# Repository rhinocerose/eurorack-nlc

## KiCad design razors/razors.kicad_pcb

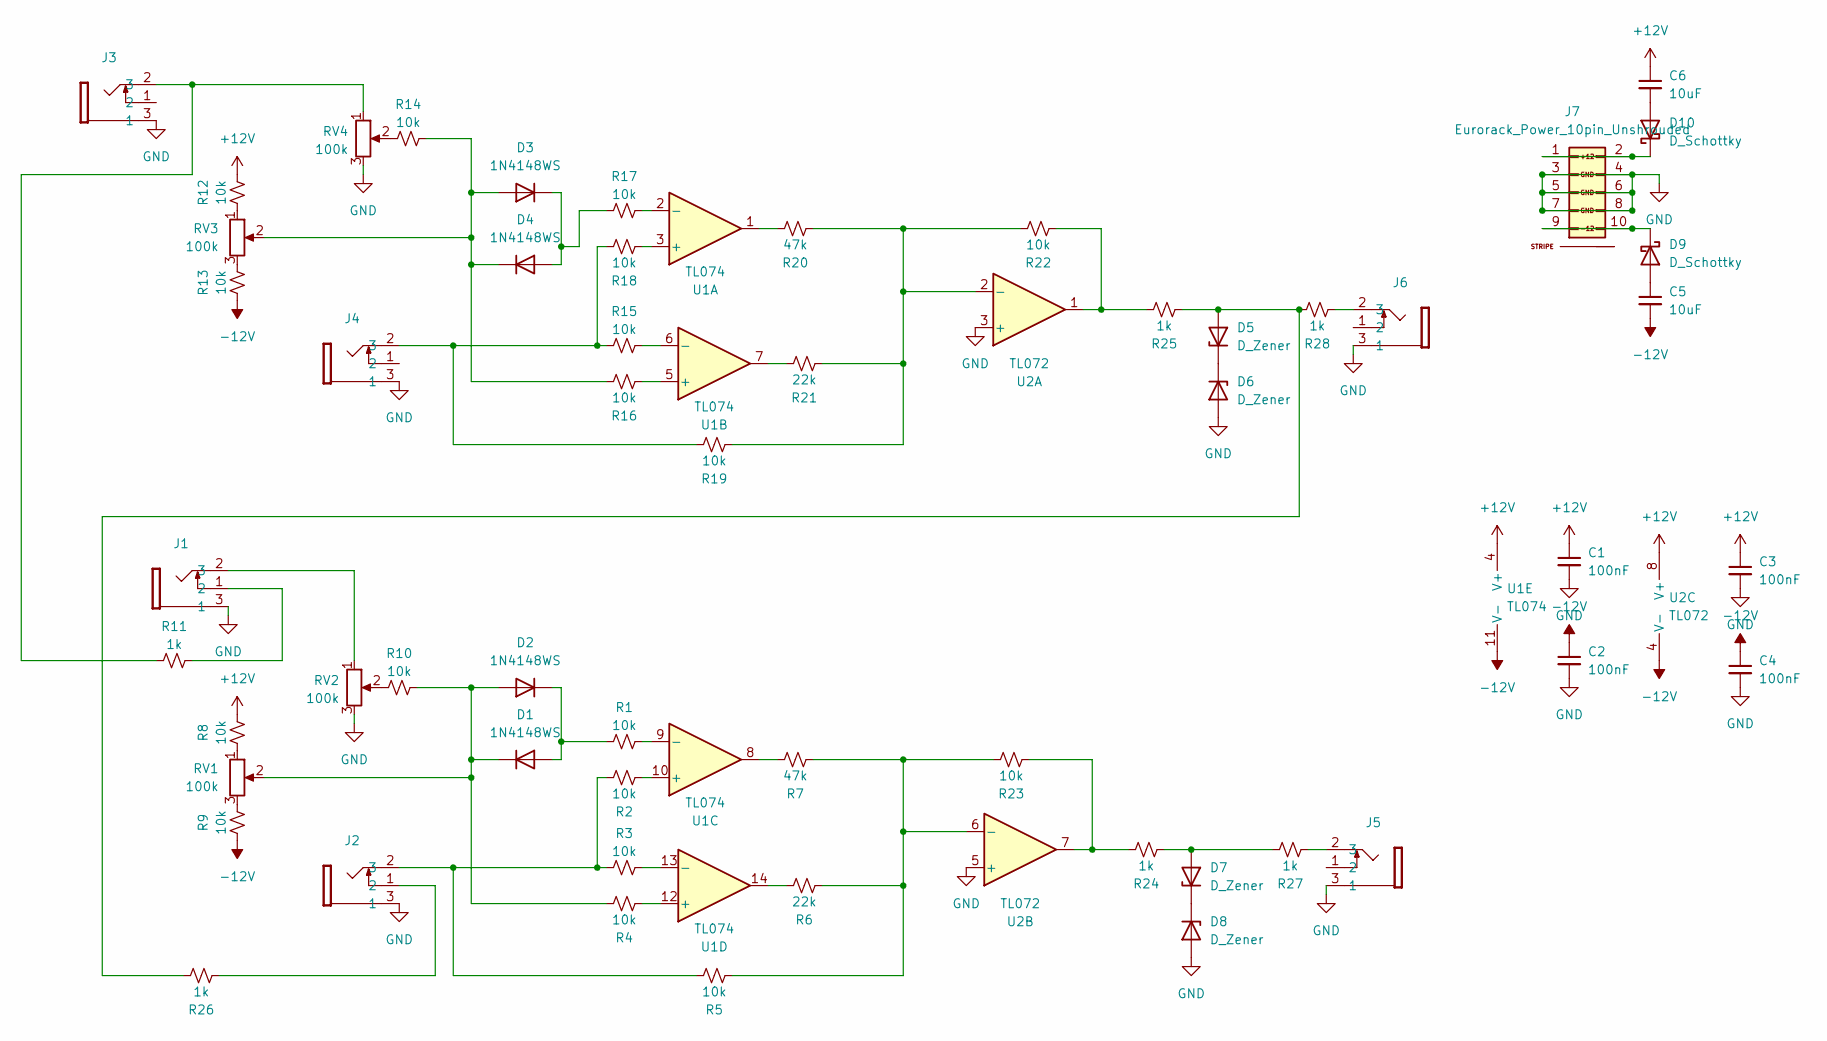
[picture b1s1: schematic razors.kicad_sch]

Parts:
C1, C2, C3, C4: 100nF; C_0603_1608Metric
C5, C6: 10uF; C_0805_2012Metric
D1, D2, D3, D4: 1N4148WS; D_SOD-323
D5, D6, D7, D8: D_Zener; D_SOD-323
D9, D10: D_Schottky; D_SOD-323
J1, J2, J3, J4, J5, J6: Thonkiconn-Jack
J7: Eurorack_Power_10pin_Unshrouded; PinHeader_2x05_P2.54mm_Vertical; Part Number 1-1002FBV0T
R1, R2, R3, R4, R5, R8, R9, R10, R12, R13, R14, R15, R16, R17, R18, R19, R22, R23: 10k; R_0603_1608Metric
R6, R21: 22k; R_0603_1608Metric
R7, R20: 47k; R_0603_1608Metric
R11, R24, R25, R26, R27, R28: 1k; R_0603_1608Metric
RV1, RV2, RV3, RV4: 100k; Potentiometer_Alps_RK09K_Single_Vertical
U1: TL074; TSSOP-14_4.4x5mm_P0.65mm
U2: TL072; TSSOP-8_4.4x3mm_P0.65mm

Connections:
+12V: C1.1, C3.1, C6.1, R8.2, R12.2, U1.4 (V+), U2.8 (V+)
-12V: C2.1, C4.1, C5.2, R9.1, R13.1, U1.11 (V-), U2.4 (V-)
GND: C1.2, C2.2, C3.2, C4.2, D6.2 (A), D8.2 (A), J1.3 (1), J2.3 (1), J3.3 (1), J4.3 (1), J5.3 (1), J6.3 (1), J7.3 (GND), J7.4 (GND), J7.5 (GND), J7.6 (GND), J7.7 (GND), J7.8 (GND), RV2.3, RV4.3, U2.3 (+), U2.5 (+)
unnamed: D1.2 (A), D2.1 (K), R1.1
unnamed: D1.1 (K), D2.2 (A), R4.2, R10.2, RV1.2
unnamed: D3.2 (A), D4.1 (K), R14.2, R16.2, RV3.2
unnamed: D3.1 (K), D4.2 (A), R17.1
unnamed: D5.2 (A), R25.1, R26.2, R28.2
unnamed: D5.1 (K), D6.1 (K)
unnamed: D7.2 (A), R24.1, R27.2
unnamed: D7.1 (K), D8.1 (K)
unnamed: C5.1, D9.2 (A)
unnamed: D9.1 (K), J7.9 (-12V), J7.10 (-12V)
unnamed: C6.2, D10.2 (A)
unnamed: D10.1 (K), J7.1 (+12V), J7.2 (+12V)
unnamed: J1.1 (2), R11.2
unnamed: J1.2 (3), RV2.1
unnamed: J2.1 (2), R26.1
unnamed: J2.2 (3), R2.2, R3.1, R5.2
unnamed: J3.2 (3), R11.1, RV4.1
unnamed: J4.2 (3), R15.1, R18.2, R19.2
unnamed: J5.2 (3), R27.1
unnamed: J6.2 (3), R28.1
unnamed: R6.2, U1.14
unnamed: R7.2, U1.8
unnamed: R8.1, RV1.1
unnamed: R9.2, RV1.3
unnamed: R10.1, RV2.2
unnamed: R12.1, RV3.1
unnamed: R13.2, RV3.3
unnamed: R14.1, RV4.2
unnamed: R20.2, U1.1
unnamed: R21.2, U1.7
unnamed: R22.1, R25.2, U2.1
unnamed: R23.1, R24.2, U2.7
unnamed: R18.1, U1.3 (+)
unnamed: R17.2, U1.2 (-)
unnamed: R16.1, U1.5 (+)
unnamed: R15.2, U1.6 (-)
unnamed: R2.1, U1.10 (+)
unnamed: R1.2, U1.9 (-)
unnamed: R4.1, U1.12 (+)
unnamed: R3.2, U1.13 (-)
unnamed: R19.1, R20.1, R21.1, R22.2, U2.2 (-)
unnamed: R5.1, R6.1, R7.1, R23.2, U2.6 (-)

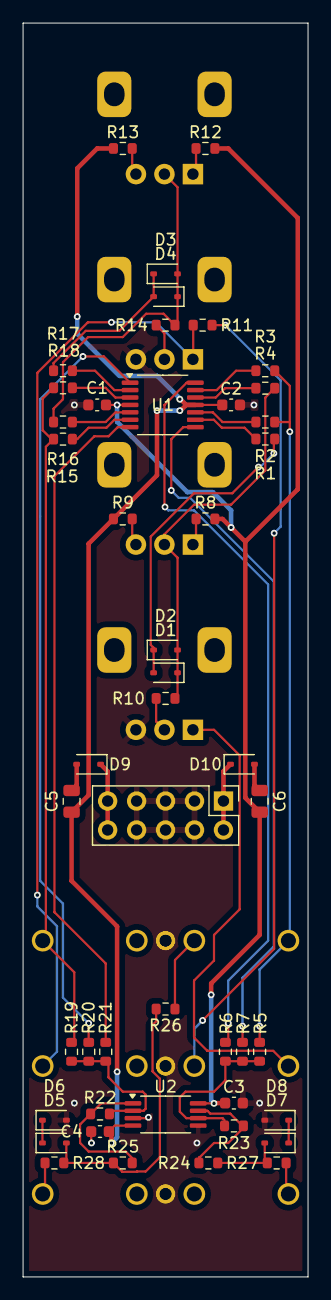
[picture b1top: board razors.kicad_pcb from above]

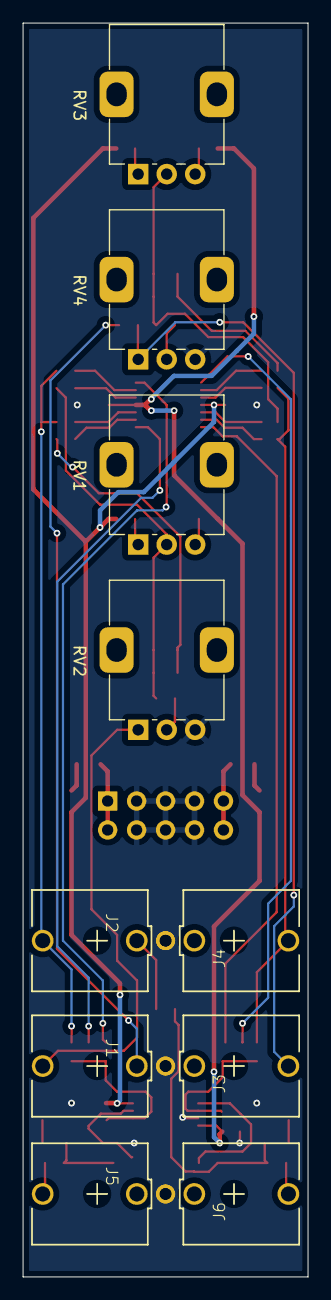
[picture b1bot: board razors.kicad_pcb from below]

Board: 2 copper layers, 25.0 x 110.0 mm, 57 parts (10 on the bottom side), 45 nets.

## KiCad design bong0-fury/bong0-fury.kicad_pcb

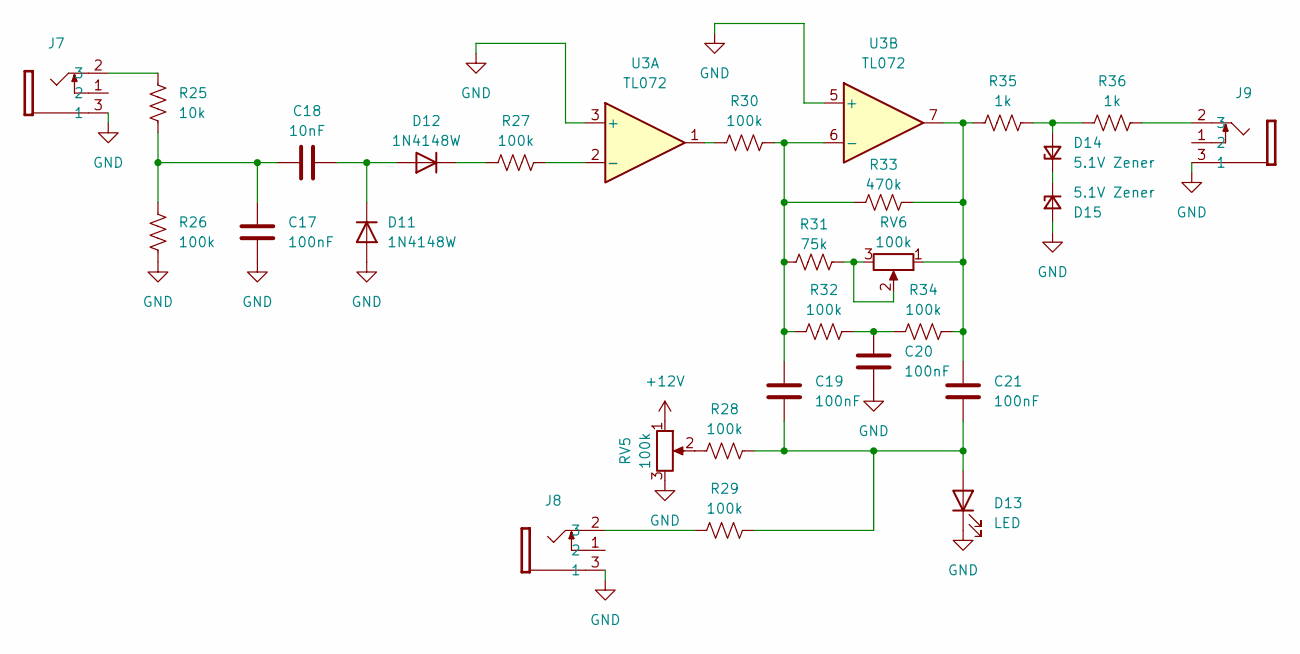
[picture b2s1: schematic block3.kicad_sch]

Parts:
C17, C19, C20, C21: 100nF; C_0603_1608Metric
C18: 10nF; C_0603_1608Metric
D11, D12: 1N4148W; D_SOD-123
D13: LED; LED_D3.0mm
D14, D15: 5.1V Zener; D_SOD-123
J7, J8, J9: Thonkiconn-Jack
R25: 10k; R_0603_1608Metric
R26, R27, R28, R29, R30, R32, R34: 100k; R_0603_1608Metric
R31: 75k; R_0603_1608Metric
R33: 470k; R_0603_1608Metric
R35, R36: 1k; R_0603_1608Metric
RV5, RV6: 100k; Potentiometer_Alps_RK09K_Single_Vertical
U3: TL072; TSSOP-8_4.4x3mm_P0.65mm

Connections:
+12V: RV5.1; also elsewhere on the board
GND: C17.2, C20.2, D11.2 (A), D13.1 (K), D15.2 (A), J7.3 (1), J8.3 (1), J9.3 (1), R26.1, RV5.3, U3.3 (+), U3.5 (+); also elsewhere on the board
unnamed: C17.1, C18.1, R25.2, R26.2
unnamed: C20.1, R32.2, R34.1
unnamed: C21.1, R33.2, R34.2, R35.1, RV6.1, U3.7
unnamed: C18.2, D11.1 (K), D12.2 (A)
unnamed: D12.1 (K), R27.1
unnamed: C19.2, C21.2, D13.2 (A), R28.2, R29.2
unnamed: D14.2 (A), R35.2, R36.1
unnamed: D14.1 (K), D15.1 (K)
unnamed: J7.2 (3), R25.1
unnamed: J8.2 (3), R29.1
unnamed: J9.2 (3), R36.2
unnamed: R28.1, RV5.2
unnamed: R30.1, U3.1
unnamed: R31.2, RV6.2, RV6.3
unnamed: R27.2, U3.2 (-)
unnamed: C19.1, R30.2, R31.1, R32.1, R33.1, U3.6 (-)

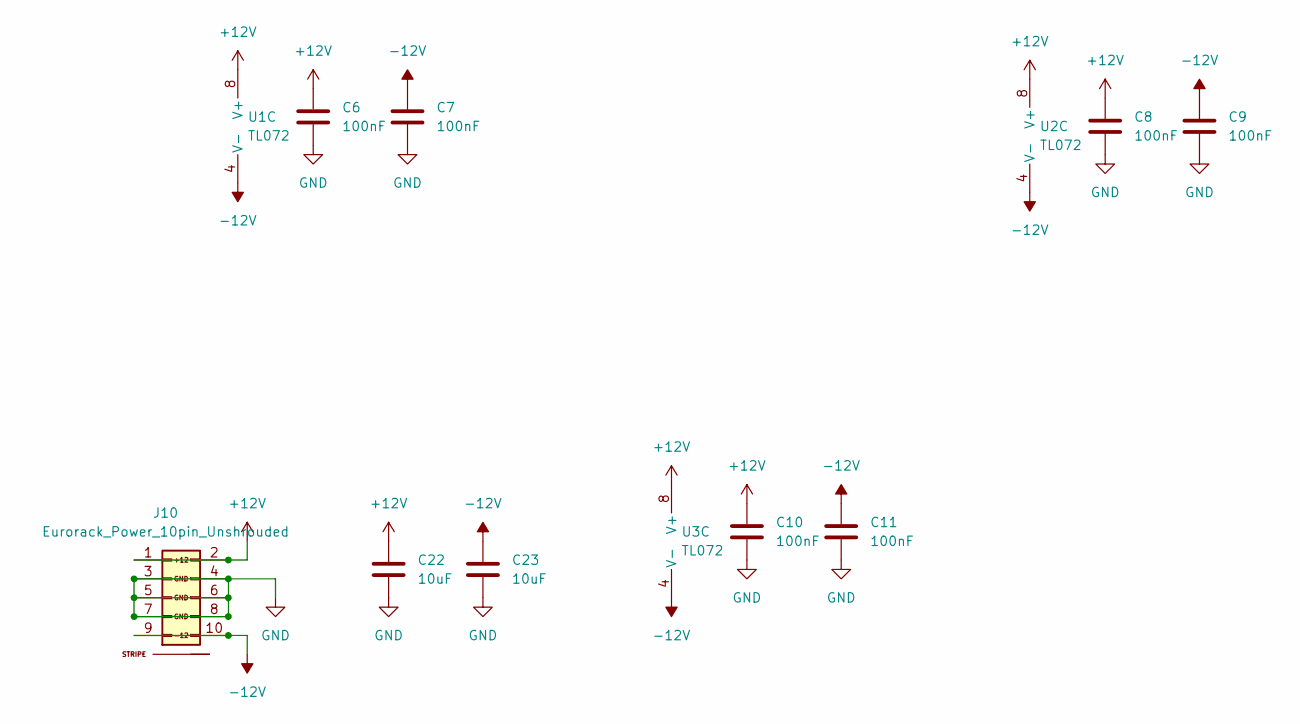
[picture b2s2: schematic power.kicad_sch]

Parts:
C6, C7, C8, C9, C10, C11: 100nF; C_0603_1608Metric
C22, C23: 10uF; C_0603_1608Metric
J10: Eurorack_Power_10pin_Unshrouded; PinSocket_2x05_P2.54mm_Vertical; Part Number 1-1002FBV0T
U1, U2, U3: TL072; TSSOP-8_4.4x3mm_P0.65mm

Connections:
+12V: C6.1, C8.1, C10.1, C22.1, J10.1 (+12V), J10.2 (+12V), U1.8 (V+), U2.8 (V+), U3.8 (V+); also elsewhere on the board
-12V: C7.1, C9.1, C11.1, C23.1, J10.9 (-12V), J10.10 (-12V), U1.4 (V-), U2.4 (V-), U3.4 (V-)
GND: C6.2, C7.2, C8.2, C9.2, C10.2, C11.2, C22.2, C23.2, J10.3 (GND), J10.4 (GND), J10.5 (GND), J10.6 (GND), J10.7 (GND), J10.8 (GND); also elsewhere on the board

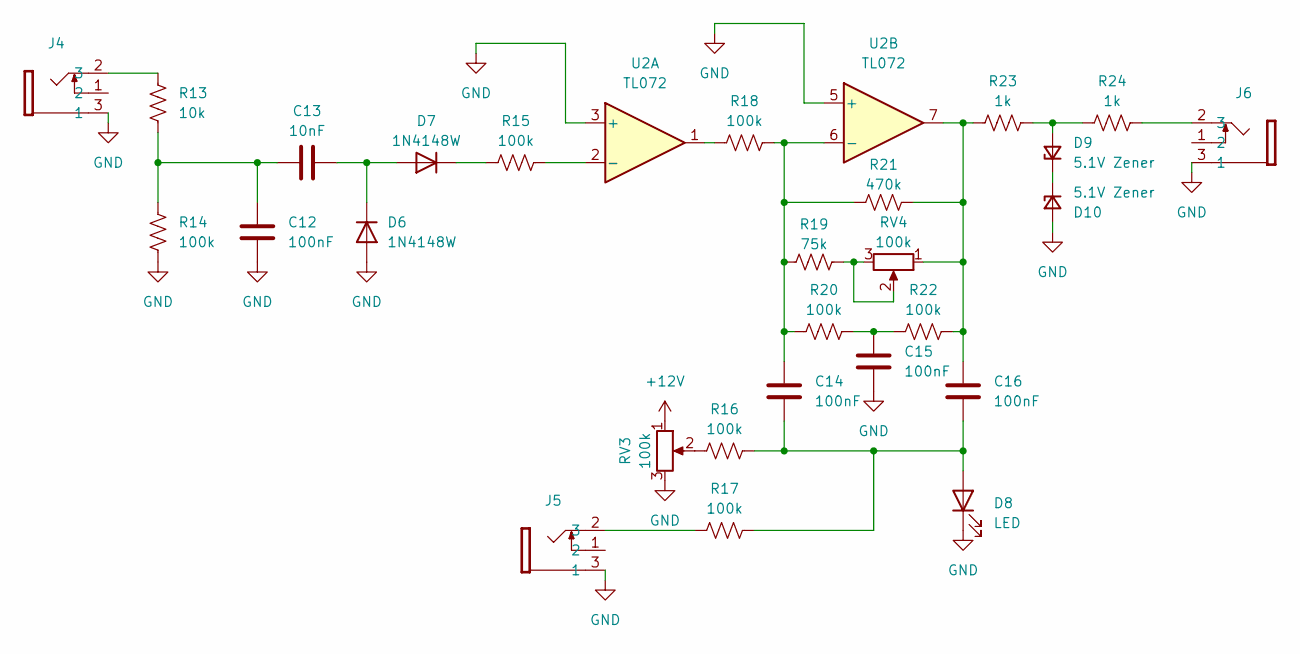
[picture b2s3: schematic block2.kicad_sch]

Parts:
C12, C14, C15, C16: 100nF; C_0603_1608Metric
C13: 10nF; C_0603_1608Metric
D6, D7: 1N4148W; D_SOD-123
D8: LED; LED_D3.0mm
D9, D10: 5.1V Zener; D_SOD-123
J4, J5, J6: Thonkiconn-Jack
R13: 10k; R_0603_1608Metric
R14, R15, R16, R17, R18, R20, R22: 100k; R_0603_1608Metric
R19: 75k; R_0603_1608Metric
R21: 470k; R_0603_1608Metric
R23, R24: 1k; R_0603_1608Metric
RV3, RV4: 100k; Potentiometer_Alps_RK09K_Single_Vertical
U2: TL072; TSSOP-8_4.4x3mm_P0.65mm

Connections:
+12V: RV3.1; also elsewhere on the board
GND: C12.2, C15.2, D6.2 (A), D8.1 (K), D10.2 (A), J4.3 (1), J5.3 (1), J6.3 (1), R14.1, RV3.3, U2.3 (+), U2.5 (+); also elsewhere on the board
unnamed: C12.1, C13.1, R13.2, R14.2
unnamed: C15.1, R20.2, R22.1
unnamed: C16.1, R21.2, R22.2, R23.1, RV4.1, U2.7
unnamed: C13.2, D6.1 (K), D7.2 (A)
unnamed: D7.1 (K), R15.1
unnamed: C14.2, C16.2, D8.2 (A), R16.2, R17.2
unnamed: D9.2 (A), R23.2, R24.1
unnamed: D9.1 (K), D10.1 (K)
unnamed: J4.2 (3), R13.1
unnamed: J5.2 (3), R17.1
unnamed: J6.2 (3), R24.2
unnamed: R16.1, RV3.2
unnamed: R18.1, U2.1
unnamed: R19.2, RV4.2, RV4.3
unnamed: R15.2, U2.2 (-)
unnamed: C14.1, R18.2, R19.1, R20.1, R21.1, U2.6 (-)

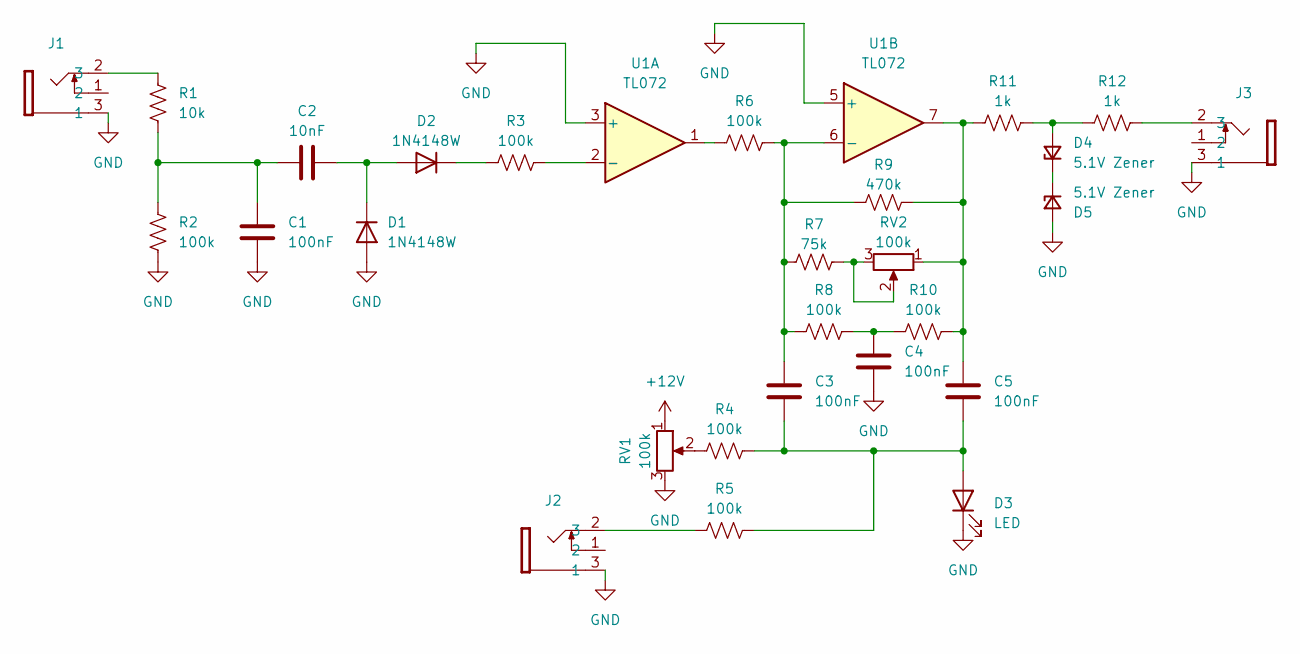
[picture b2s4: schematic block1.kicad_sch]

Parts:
C1, C3, C4, C5: 100nF; C_0603_1608Metric
C2: 10nF; C_0603_1608Metric
D1, D2: 1N4148W; D_SOD-123
D3: LED; LED_D3.0mm
D4, D5: 5.1V Zener; D_SOD-123
J1, J2, J3: Thonkiconn-Jack
R1: 10k; R_0603_1608Metric
R2, R3, R4, R5, R6, R8, R10: 100k; R_0603_1608Metric
R7: 75k; R_0603_1608Metric
R9: 470k; R_0603_1608Metric
R11, R12: 1k; R_0603_1608Metric
RV1, RV2: 100k; Potentiometer_Alps_RK09K_Single_Vertical
U1: TL072; TSSOP-8_4.4x3mm_P0.65mm

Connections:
+12V: RV1.1; also elsewhere on the board
GND: C1.2, C4.2, D1.2 (A), D3.1 (K), D5.2 (A), J1.3 (1), J2.3 (1), J3.3 (1), R2.1, RV1.3, U1.3 (+), U1.5 (+); also elsewhere on the board
unnamed: C1.1, C2.1, R1.2, R2.2
unnamed: C4.1, R8.2, R10.1
unnamed: C5.1, R9.2, R10.2, R11.1, RV2.1, U1.7
unnamed: C2.2, D1.1 (K), D2.2 (A)
unnamed: D2.1 (K), R3.1
unnamed: C3.2, C5.2, D3.2 (A), R4.2, R5.2
unnamed: D4.2 (A), R11.2, R12.1
unnamed: D4.1 (K), D5.1 (K)
unnamed: J1.2 (3), R1.1
unnamed: J2.2 (3), R5.1
unnamed: J3.2 (3), R12.2
unnamed: R4.1, RV1.2
unnamed: R6.1, U1.1
unnamed: R7.2, RV2.2, RV2.3
unnamed: R3.2, U1.2 (-)
unnamed: C3.1, R6.2, R7.1, R8.1, R9.1, U1.6 (-)

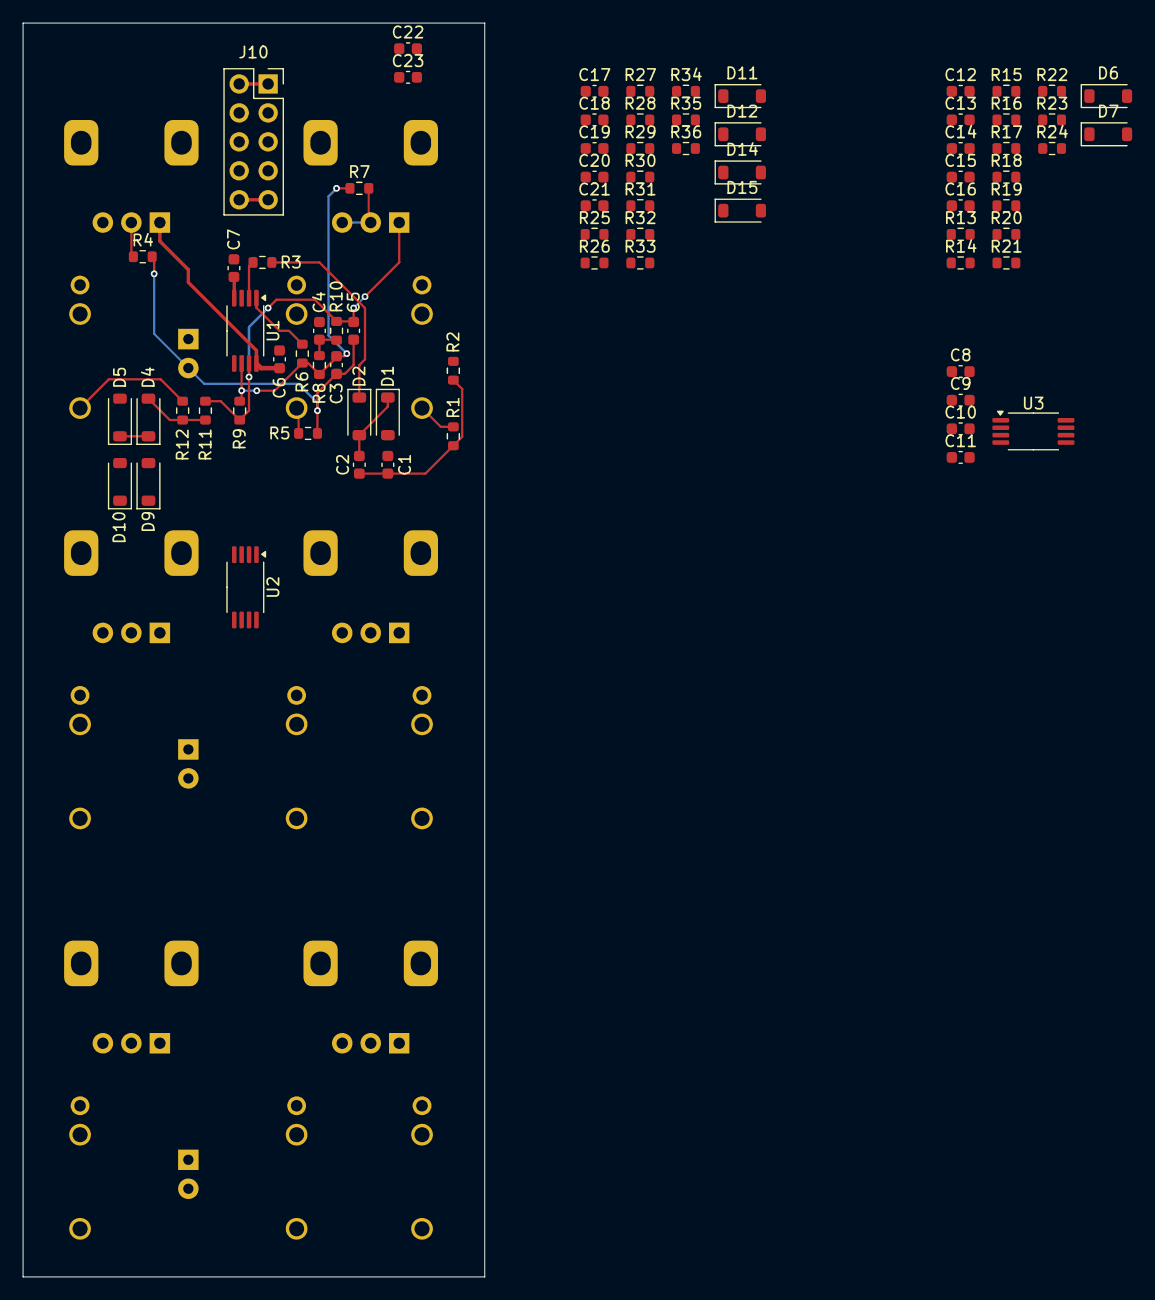
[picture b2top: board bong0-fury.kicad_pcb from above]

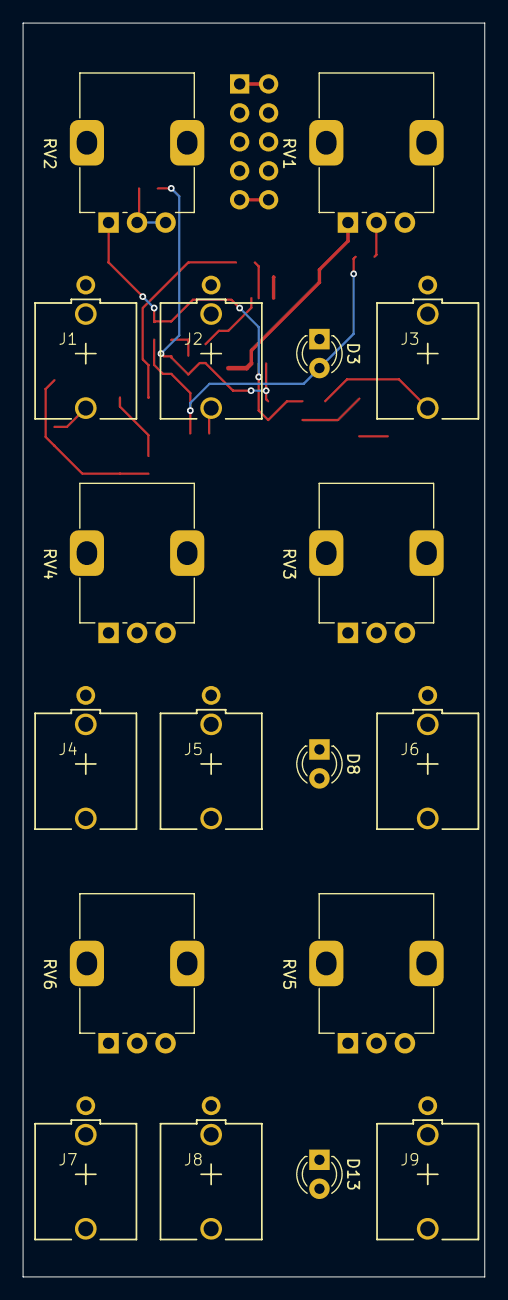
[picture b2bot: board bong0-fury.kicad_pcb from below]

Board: 2 copper layers, 40.5 x 110.0 mm, 93 parts (18 on the bottom side), 51 nets.

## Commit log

2025-11-11 Added schematics and started Bongo Fury
2025-11-12 Razors laid out
2025-11-24 Unknown changes
